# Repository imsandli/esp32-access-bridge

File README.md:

# AccessBridge

**Zigbee dry-contact bridge between a UniFi Access UA-Hub and Home Assistant.**
When the UA-Hub grants access, it closes a potential-free relay contact.
AccessBridge detects the closure and reports it over Zigbee to Zigbee2MQTT.
Home Assistant can then unlatch a Nuki Smart Lock Pro 4. No cloud and no Wi-Fi.

| Part | Name | Version | Licence |
|---|---|---|---|
| Hardware | AccessBridge C6 (Seeed XIAO ESP32C6 carrier) | HW-1.1, PCB Rev B | [CERN-OHL-S-2.0](LICENSE-HARDWARE) |
| Enclosure | 3D-printable case, DIN-rail or wall-screw variant | for HW-1.1 | [CERN-OHL-S-2.0](LICENSE-HARDWARE) |
| Firmware | AccessBridge Zigbee (ESPHome 2026.9.1) | FW-1.0.0 | [MIT](LICENSE) |
| Integrations | Home Assistant blueprints, Zigbee2MQTT notes | - | [MIT](LICENSE) |

> [!WARNING]
> **Not hardware-tested.** Rev B has passed ERC/DRC, the firmware compiles,
> and the Home Assistant logic is covered by automated tests. No board has
> been manufactured or measured yet, and nothing has been tested with a real
> UA-Hub or Nuki. See [compatibility status](#compatibility-status).
>
> **Security:** this device is part of a door access chain. Whoever can short
> the relay wires, or controls your Zigbee/MQTT/Home Assistant, can open the
> door. Read [docs/security.md](docs/security.md) before use. **Never connect
> mains voltage to this board.**

## How it works

```mermaid
flowchart LR
  R[UniFi reader] --> H[UA-Hub]
  H -- "dry relay COM/NO" --> B[AccessBridge C6]
  H -- "12 V LINE (power)" --> B
  B -- "Zigbee end device" --> Z[Zigbee2MQTT >= 2.8.0]
  Z -- MQTT --> HA[Home Assistant<br/>nuki-unlock blueprint]
  HA -- lock.open --> N[Nuki Smart Lock Pro 4]
```

* The contact loop is powered by the board itself (optocoupler, about 3.3 mA),
  so no external voltage is needed on the relay contact.
* The firmware reports the contact **state** and a **pulse counter** of new
  closures. Home Assistant only unlatches on a +1 step of the counter that
  passes the freshness, cooldown and enable checks. Restarts, rejoins and
  restored states never unlatch. Details: [docs/security.md](docs/security.md).
* Power from the UA-Hub 12 V **or** a USB-C charger (J6, power only; the whole
  board including the contact inputs runs on USB for bench tests). Firmware is
  flashed through the XIAO's own USB-C, next to J6 on the same edge.
* Optional: doorbell input (230 V bells via a certified coupling relay; the
  doorbell blueprint also accepts other sensors, see
  [wiring](hardware/docs/wiring.md#doorbell-optional)), selectable contact
  wetting current (JP3-JP5), a
  door-position (DPS) port that works as an input or as an isolated contact
  output, a 12 V open-drain output, and a Qwiic I2C port.

More detail: [docs/architecture.md](docs/architecture.md).

## Supported hardware

| Component | Status |
|---|---|
| UniFi Access **UA-Hub** (classic), LINE 12 V output + dry Lock/Aux relay | designed for; LINE "always on" must be measured on site |
| UA-Hub Door / Gate Hub / Enterprise Hub | not covered (different I/O) |
| Seeed Studio XIAO ESP32C6 | required (socketed) |
| Zigbee2MQTT >= 2.8.0 | designed for (generated definition, no converter) |
| ZHA | not covered by the docs; the firmware uses standard clusters |
| Nuki Smart Lock Pro 4 via the HA Nuki integration (`lock.open`) | designed for |

## Compatibility status

| Level | HW-1.1 Rev B + FW-1.0.0 |
|---|---|
| Statically checked (ERC, DRC with parity, ESPHome config, HA check_config) | **yes** |
| Enclosure fit-checked against the PCB STEP (CI) | **yes** |
| Firmware compiled (CI) | **yes** |
| Software-tested (HA blueprint behaviour tests, 15/15) | **yes** |
| Electrically tested | no |
| Tested with Zigbee2MQTT | no |
| Tested with a real UA-Hub | no |
| Tested with a Nuki | no |

Test plan and record: [docs/testing.md](docs/testing.md).

## Project status (development workflow)

| # | Step | Status |
|---|---|---|
| 1 | Feasibility and datasheet review | done; open points: UA-Hub LINE always-on, XIAO antenna position, Hammond boss positions, live LCSC stock |
| 2 | Schematic | done (`hardware/kicad/accessbridge.kicad_sch`) |
| 3 | ERC | done: 0 errors, 0 warnings |
| 4 | PCB layout | done: 96 x 56 mm, 2 layers (Rev B = Rev A + USB-C power input) |
| 5 | DRC | done: 0 violations, 0 unconnected, 0 parity issues |
| 6 | Fabrication data and BOM | done: Gerber ZIP, drill, JLCPCB BOM/CPL (reproducible, checked in CI) |
| 7 | Firmware implemented and compiled | done (ESPHome 2026.9.1, CI) |
| 8 | Zigbee2MQTT compatibility test | open: needs hardware |
| 9 | Home Assistant example | done (blueprints, check_config, 15 behaviour tests) |
| 10 | Security tests | documented; software part done; hardware part open |
| 11 | Enclosure and mounting check | 3D-printable case (DIN-rail and wall variants) designed and fit-checked against the PCB STEP in CI; not printed yet. Hammond 1591XXD documented as alternative |
| 12 | Release artifacts | workflow ready; first release after the hardware tests |

## Wiring (classic UA-Hub)

| AccessBridge | UA-Hub |
|---|---|
| J1-1 `+12V` | LINE 12V (+) |
| J1-2 `GND` | LINE 12V (-) |
| J1-3 `RELAY COM` | Lock (or Aux) relay COM, **dry mode** |
| J1-4 `RELAY NO` | Lock (or Aux) relay NO |
| J6 USB-C (optional) | any USB-C charger, 5 V, power only, e.g. for bench tests |

Full instructions, doorbell and DPS options: [hardware/docs/wiring.md](hardware/docs/wiring.md).

## Firmware installation

```sh
pip install esphome==2026.9.1
cd firmware/esphome
esphome run accessbridge.yaml      # build + flash over USB-C
```

Or flash a release binary with `esptool.py`. See [docs/installation.md](docs/installation.md).

## Zigbee2MQTT pairing

1. Permit join in Zigbee2MQTT (>= 2.8.0).
2. Power the AccessBridge. The status LED blinks fast until it has joined.
3. The device appears as `esphome` / `accessbridge` with a generated
   definition, with no converter needed.
4. Permit join off. To re-pair, hold PAIR for 5-15 s.

Details and expected exposes: [integrations/zigbee2mqtt](integrations/zigbee2mqtt/README.md).

## Home Assistant example

Import the blueprint [`nuki-unlock.yaml`](integrations/home-assistant/automations/nuki-unlock.yaml)
and select the `relay_pulses` sensor, the `relay_contact` binary sensor and
your Nuki lock. Every ignored pulse is logged with its reason, and unconfirmed
unlatch commands are logged as errors.
See [integrations/home-assistant](integrations/home-assistant/README.md).

## Manufacturing

| | |
|---|---|
| Gerber + drill ZIP (JLCPCB) | [hardware/manufacturing/accessbridge-c6-HW-1.1-revB-gerbers.zip](hardware/manufacturing/accessbridge-c6-HW-1.1-revB-gerbers.zip) |
| JLCPCB BOM / CPL | [bom](hardware/manufacturing/bom/), [pick-and-place](hardware/manufacturing/pick-and-place/) |
| Schematic PDF | [hardware/docs/schematic.pdf](hardware/docs/schematic.pdf) |
| Dimension drawing | [hardware/enclosure/drawings](hardware/enclosure/drawings/accessbridge-c6-dimensions.pdf) |
| Ordering and assembly | [hardware/docs/assembly.md](hardware/docs/assembly.md) |
| Enclosure (3D print, STL/STEP) | [hardware/enclosure](hardware/enclosure/README.md): DIN-rail or wall-screw base, lid, plunger, cable clamp |
| Cost estimate (2/5/10 units) | [hardware/docs/cost-estimate.md](hardware/docs/cost-estimate.md) |
| Releases | [GitHub releases](https://github.com/imsandli/esp32-access-bridge/releases), [releases/README.md](releases/README.md) |

## Repository layout

```
hardware/      KiCad sources, fabrication data (generated), docs, 3D-printed enclosure (CadQuery)
firmware/      ESPHome configuration (FW-1.0.0); ESP-IDF fallback plan
integrations/  Home Assistant blueprints + tests, Zigbee2MQTT notes
docs/          architecture, security, installation, configuration, testing
scripts/       ERC/DRC validation, Gerber/BOM export (KiCad CLI, Docker fallback)
releases/      release process and version scheme
```

## Contributing and licences

See [CONTRIBUTING.md](CONTRIBUTING.md) and [CHANGELOG.md](CHANGELOG.md).
Software (firmware, scripts, integrations, docs) is MIT. Hardware design files
under `hardware/` are CERN-OHL-S-2.0.

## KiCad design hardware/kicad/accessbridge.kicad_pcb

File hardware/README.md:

# AccessBridge C6: hardware

**HW-1.1, PCB Rev B**, KiCad 9.0.9, 2 layers, 96 x 56 mm, CERN-OHL-S-2.0.

Rev B = Rev A plus a **USB-C power input** (J6, 5 V, power only) in a 10 mm
wider right-hand strip. All Rev A parts kept their positions, and Rev A
tracks were kept except around the rewired loop resistors (R10/R14/R18 now on
`V_LOOP`) and R18's neighbourhood.

| | |
|---|---|
| Schematic (PDF) | [docs/schematic.pdf](docs/schematic.pdf) |
| Pinout | [docs/pinout.md](docs/pinout.md) |
| Wiring (UA-Hub) | [docs/wiring.md](docs/wiring.md) |
| Power budget | [docs/power-budget.md](docs/power-budget.md) |
| Assembly / ordering | [docs/assembly.md](docs/assembly.md) |
| Fabrication data | [manufacturing/](manufacturing/README.md) |
| Enclosure (3D print, DIN or wall variant) | [enclosure/](enclosure/README.md) |
| Dimension drawing | [enclosure/drawings/accessbridge-c6-dimensions.pdf](enclosure/drawings/accessbridge-c6-dimensions.pdf) |

## Status

| Check | Status |
|---|---|
| ERC (KiCad 9.0.9, all severities) | **0 errors, 0 warnings** (local and CI) |
| DRC incl. schematic parity (all severities) | **0 violations, 0 unconnected, 0 parity issues** (local and CI) |
| Fabrication data reproducible from sources | **yes**, checked in CI (`scripts/tools/check_generated.py`) |
| Prototype manufactured | no |
| Electrically tested | **no** |

## Source files (`kicad/`)

| File | Content |
|---|---|
| `accessbridge.kicad_pro` | Project: design rules (JLCPCB-safe: 0.2 mm clearance/track, 0.3 mm drill), net classes (Power 0.5 mm, Field 0.3 mm clearance), text variables `HW_VERSION`, `PCB_REV` |
| `accessbridge.kicad_sch` | Schematic (single A3 sheet, framed blocks: connectors, power, MCU, contact inputs, DPS port, output) |
| `accessbridge.kicad_pcb` | Layout |
| `symbols/AccessBridge.kicad_sym` | `XIAO_ESP32C6` symbol (pin names = XIAO D-pin / GPIO) |
| `footprints/AccessBridge.pretty/` | `XIAO_ESP32C6_Socketed` (pad geometry from the Seeed OPL library, 3D = 2x KiCad PinSocket_1x07; includes the antenna keep-out between the pin rows) |
| `sym-lib-table`, `fp-lib-table` | Project libraries via `${KIPRJMOD}` (relative paths) |

All other symbols, footprints and 3D models come from the KiCad 9 standard
libraries (`kicad/kicad:9.0.9-full` contains the 3D models). `3dmodels/` is
reserved for project models; none are needed. The XIAO module itself
has no 3D model: only its sockets are shown.

## Design notes

* **Antenna:** the XIAO's ceramic antenna end (opposite USB-C) has no copper
  between the pin rows, no copper pour below the module end, and a 9 mm
  copper keep-out beyond the module edge on both layers. The module sits about
  8.5 mm above the carrier on its sockets. The exact antenna position on the
  module should be confirmed with a physical sample (open point).
* **Contact inputs:** see [docs/architecture.md](../docs/architecture.md),
  decision A4, and the isolation assessment.
* **Reference designators** are on the Fab layer (assembly drawing
  `docs/assembly-top.pdf`). The silkscreen carries only functional labels,
  so nothing is printed on pads.
* **USB-C power (J6):** VBUS -> PTC F2 (500 mA) + TVS D14 -> D13 into `+5V_XIAO`
  (diode-OR with D3 from the buck) and D16 into `V_LOOP` (diode-OR with D15 from
  +12 V), so the contact inputs also work on USB. CC1/CC2 have 5.1 kΩ to GND
  (USB-C sink). J4 OUT+ stays 12 V only. There is no USB data: the XIAO does not
  route D+/D- to its pins, so firmware goes through the XIAO's own USB-C, which
  sits 15 mm from J6 on the same board edge.
* **Revision marking:** `AccessBridge C6 HW-1.1 Rev B` on the top silkscreen
  and in the title blocks.

## Checks (KiCad CLI)

```sh
scripts/validate-hardware.sh   # ERC + DRC with --schematic-parity, fails on any violation
scripts/export-bom.sh          # full BOM, JLCPCB BOM/CPL, manual assembly list
scripts/export-gerbers.sh      # Gerbers, drill, ZIP, schematic PDF, drawings, 3D renders, PCB STEP
scripts/export-enclosure.sh    # 3D-printed enclosure: STEP/STL, previews, fit check (CadQuery)
```

The scripts use a native KiCad 9 if available, otherwise the pinned Docker
image `kicad/kicad:9.0.9`. The raw commands they wrap are, for example:

```sh
kicad-cli sch erc --severity-all --exit-code-violations hardware/kicad/accessbridge.kicad_sch
kicad-cli pcb drc --severity-all --schematic-parity --exit-code-violations hardware/kicad/accessbridge.kicad_pcb
```

## How Rev A and Rev B were created

Rev A's schematic and initial layout were generated from
[`tools/design.py`](tools/design.py) by the scripts in [`tools/`](tools/README.md)
and routed with Freerouting. Rev B was an incremental change of that board
(`gen_pcb.py update`, then only the new connections routed). From now on, edit
the KiCad files directly.
The generators are kept for transparency only.

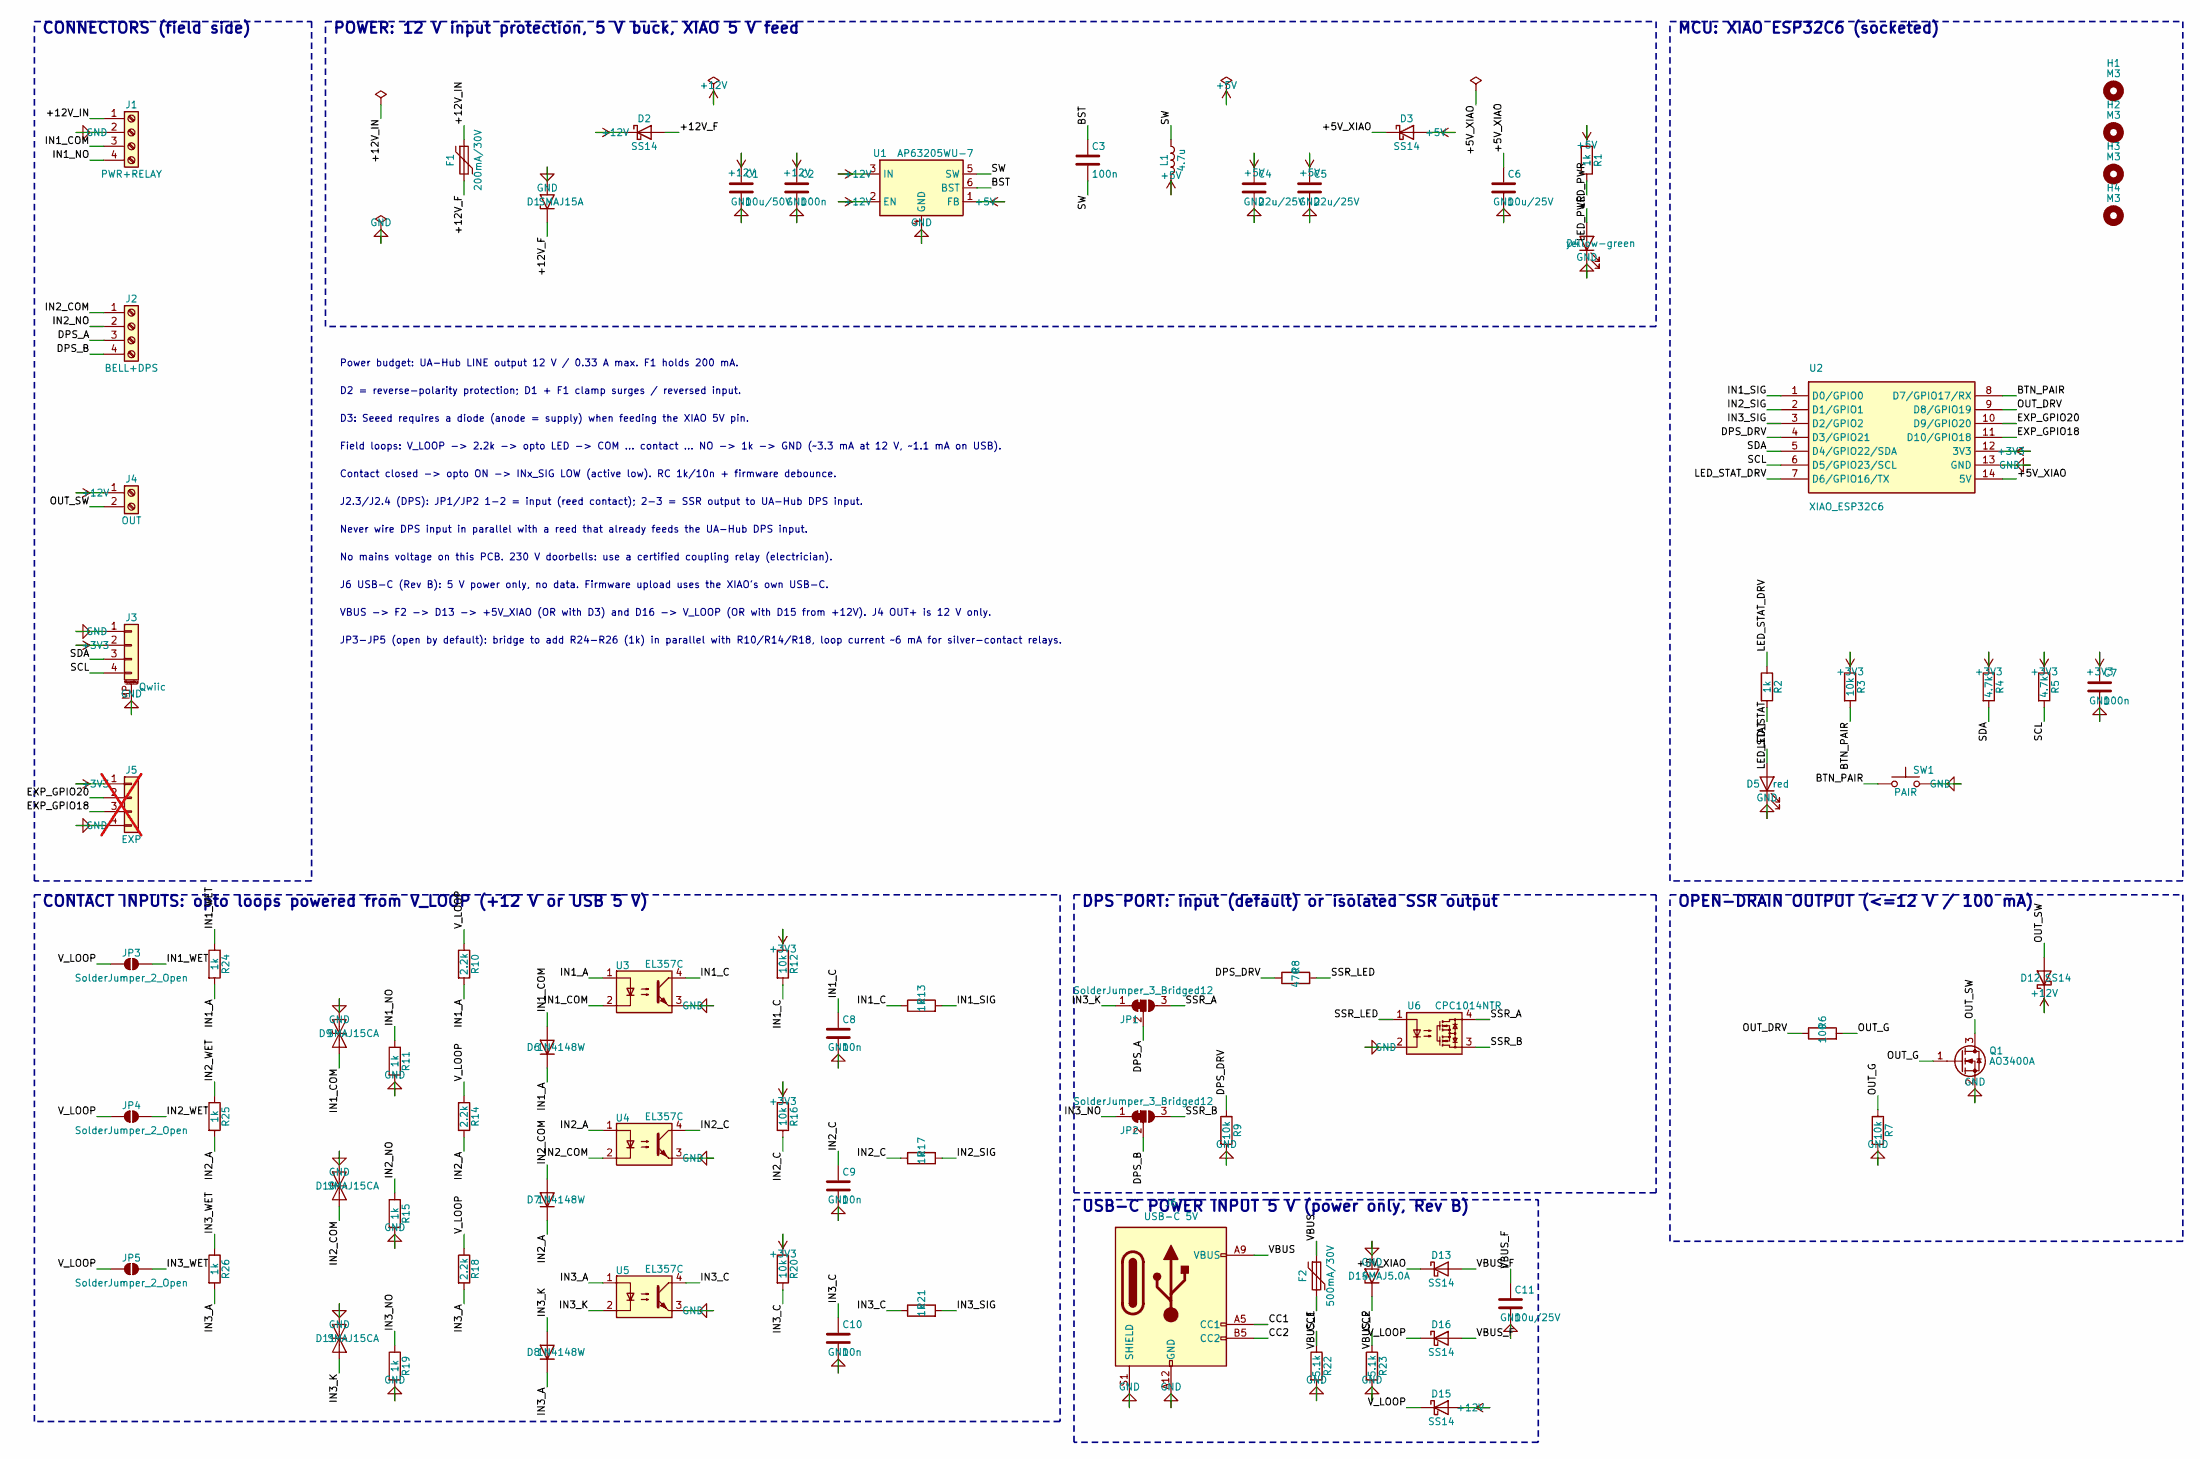
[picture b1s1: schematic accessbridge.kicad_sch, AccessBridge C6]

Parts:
C1: 10u/50V; C_1206_3216Metric; MPN CL31A106KBHNNNE; LCSC C13585
C2, C3, C7: 100n; C_0603_1608Metric; MPN CC0603KRX7R9BB104; LCSC C14663
C4, C5: 22u/25V; C_0805_2012Metric; MPN CL21A226MAQNNNE; LCSC C45783
C6, C11: 10u/25V; C_0805_2012Metric; MPN CL21A106KAYNNNE; LCSC C15850
C8, C9, C10: 10n; C_0603_1608Metric; MPN 0603B103K500NT; LCSC C57112
D1: SMAJ15A; D_SMA; MPN SMAJ15A; LCSC C148216
D2, D3, D12, D13, D15, D16: SS14; D_SMA; MPN SS14; LCSC C2480
D4: yellow-green; LED_0603_1608Metric; MPN KT-0603YG; LCSC C2289
D5: red; LED_0603_1608Metric; MPN KT-0603R; LCSC C2286
D6, D7, D8: 1N4148W; D_SOD-123; MPN 1N4148W; LCSC C81598
D9, D10, D11: SMAJ15CA; D_SMA; MPN SMAJ15CA; LCSC C110044
D14: SMAJ5.0A; D_SMA; MPN SMAJ5.0A; LCSC C83329
F1: 200mA/30V; Fuse_1206_3216Metric; MPN BSMD1206-020-30V; LCSC C883118
F2: 500mA/30V; Fuse_1206_3216Metric; MPN BSMD1206-050-30V; LCSC C883126
H1, H2, H3, H4: M3; MountingHole_3.2mm_M3; MPN M3 mounting hole; LCSC_Status pcb
J1: PWR+RELAY; TerminalBlock_Phoenix_MKDS-1,5-4-5.08_1x04_P5.08mm_Horizont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; MPN MKDS 1,5/ 4-5,08 (1715747) or 5.08 mm e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; LCSC_Status manual
J2: BELL+DPS; TerminalBlock_Phoenix_MKDS-1,5-4-5.08_1x04_P5.08mm_Horizont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; MPN MKDS 1,5/ 4-5,08 (1715747) or 5.08 mm e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; LCSC_Status manual
J3: Qwiic; JST_SH_SM04B-SRSS-TB_1x04-1MP_P1.00mm_Horizontal; MPN SM04B-SRSS-TB(LF)(SN); LCSC C160404
J4: OUT; TerminalBlock_Phoenix_MKDS-1,5-2-5.08_1x02_P5.08mm_Horizont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; MPN MKDS 1,5/ 2-5,08 (1715721) or 5.08 mm e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; LCSC_Status manual
J5: EXP; PinHeader_1x04_P2.54mm_Vertical; MPN 2.54 mm 1x4 pin header; LCSC_Status manual; not fitted
J6: USB-C 5V; USB_C_Receptacle_GCT_USB4125-xx-x_6P_TopMnt_Horizontal; MPN USB4125-GF-A; LCSC C3151650
JP1, JP2: SolderJumper_3_Bridged12; SolderJumper-3_P1.3mm_Bridged12_RoundedPad1.0x1.5mm_NumberL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; MPN PCB solder jumper; LCSC_Status pcb
JP3, JP4, JP5: SolderJumper_2_Open; SolderJumper-2_P1.3mm_Open_RoundedPad1.0x1.5mm; MPN PCB solder jumper; LCSC_Status pcb
L1: 4.7u; L_Changjiang_FNR4030S; MPN SWPA4030S4R7MT; LCSC C57269
Q1: AO3400A; SOT-23; MPN AO3400A; LCSC C20917
R1, R2, R11, R13, R15, R17, R19, R21: 1k; R_0603_1608Metric; MPN 0603WAF1001T5E; LCSC C21190
R3, R7, R9, R12, R16, R20: 10k; R_0603_1608Metric; MPN 0603WAF1002T5E; LCSC C25804
R4, R5: 4.7k; R_0603_1608Metric; MPN 0603WAF4701T5E; LCSC C23162
R6: 100; R_0603_1608Metric; MPN 0603WAF1000T5E; LCSC C22775
R8: 470; R_0603_1608Metric; MPN 0603WAF4700T5E; LCSC C23179
R10, R14, R18: 2.2k; R_0603_1608Metric; MPN 0603WAF2201T5E; LCSC C4190
R22, R23: 5.1k; R_0603_1608Metric; MPN 0603WAF5101T5E; LCSC C23186
R24, R25, R26: 1k; R_1206_3216Metric; MPN 1206W4F1001T5E; LCSC C4410
SW1: PAIR; SW_Push_1P1T_XKB_TS-1187A; MPN TS-1187A-B-A-B; LCSC C318884
U1: AP63205WU-7; TSOT-23-6; MPN AP63205WU-7; LCSC C2071056
U2: XIAO_ESP32C6; XIAO_ESP32C6_Socketed; MPN 113991254 (module) + 2x female header 1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; LCSC_Status manual
U3, U4, U5: EL357C; SO-4_4.4x3.6mm_P2.54mm; MPN EL357C; LCSC C725794
U6: CPC1014NTR; SOP-4_3.8x4.1mm_P2.54mm; MPN CPC1014NTR; LCSC C2760365

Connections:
+3V3: C7.1, J3.2, J5.1, R3.1, R4.1, R5.1, R12.1, R16.1, R20.1, U2.12 (3V3)
+5V: C4.1, C5.1, D3.2 (A), L1.2, R1.1, U1.1 (FB)
+12V: C1.1, C2.1, D2.1 (K), D12.1 (K), D15.2 (A), J4.1, U1.2 (EN), U1.3 (IN)
/+5V_XIAO: C6.1, D3.1 (K), D13.1 (K), U2.14 (5V)
/+12V_F: D1.1 (A1), D2.2 (A), F1.2
/+12V_IN: F1.1, J1.1
/BST: C3.1, U1.6 (BST)
/BTN_PAIR: R3.2, SW1.1, U2.8 (D7/GPIO17/RX)
/CC1: J6.A5 (CC1), R22.1
/CC2: J6.B5 (CC2), R23.1
/DPS_A: J2.3, JP1.2 (C)
/DPS_B: J2.4, JP2.2 (C)
/DPS_DRV: R8.1, R9.1, U2.4 (D3/GPIO21)
/EXP_GPIO18: J5.3, U2.11 (D10/GPIO18)
/EXP_GPIO20: J5.2, U2.10 (D9/GPIO20)
/IN1_A: D6.1 (K), R10.2, R24.2, U3.1
/IN1_C: C8.1, R12.2, R13.1, U3.4
/IN1_COM: D6.2 (A), D9.1 (A1), J1.3, U3.2
/IN1_NO: J1.4, R11.1
/IN1_SIG: R13.2, U2.1 (D0/GPIO0)
/IN1_WET: JP3.2 (B), R24.1
/IN2_A: D7.1 (K), R14.2, R25.2, U4.1
/IN2_C: C9.1, R16.2, R17.1, U4.4
/IN2_COM: D7.2 (A), D10.1 (A1), J2.1, U4.2
/IN2_NO: J2.2, R15.1
/IN2_SIG: R17.2, U2.2 (D1/GPIO1)
/IN2_WET: JP4.2 (B), R25.1
/IN3_A: D8.1 (K), R18.2, R26.2, U5.1
/IN3_C: C10.1, R20.2, R21.1, U5.4
/IN3_K: D8.2 (A), D11.1 (A1), JP1.1 (A), U5.2
/IN3_NO: JP2.1 (A), R19.1
/IN3_SIG: R21.2, U2.3 (D2/GPIO2)
/IN3_WET: JP5.2 (B), R26.1
/LED_PWR: D4.2 (A), R1.2
/LED_STAT: D5.2 (A), R2.2
/LED_STAT_DRV: R2.1, U2.7 (D6/GPIO16/TX)
/OUT_DRV: R6.1, U2.9 (D8/GPIO19)
/OUT_G: Q1.1 (G), R6.2, R7.1
/OUT_SW: D12.2 (A), J4.2, Q1.3 (D)
/SCL: J3.4, R5.2, U2.6 (D5/GPIO23/SCL)
/SDA: J3.3, R4.2, U2.5 (D4/GPIO22/SDA)
/SSR_A: JP1.3 (B), U6.4
/SSR_B: JP2.3 (B), U6.3
/SSR_LED: R8.2, U6.1
/SW: C3.2, L1.1, U1.5 (SW)
/VBUS: F2.1, J6.A9 (VBUS), J6.B9 (VBUS)
/VBUS_F: C11.1, D13.2 (A), D14.1 (A1), D16.2 (A), F2.2
/V_LOOP: D15.1 (K), D16.1 (K), JP3.1 (A), JP4.1 (A), JP5.1 (A), R10.1, R14.1, R18.1
GND: C1.2, C2.2, C4.2, C5.2, C6.2, C7.2, C8.2, C9.2, C10.2, C11.2, D1.2 (A2), D4.1 (K), D5.1 (K), D9.2 (A2), D10.2 (A2), D11.2 (A2), D14.2 (A2), J1.2, J3.1, J3.MP (MountPin), J5.4, J6.A12 (GND), J6.B12 (GND), J6.S1 (SHIELD), Q1.2 (S), R7.2, R9.2, R11.2, R15.2, R19.2, R22.2, R23.2, SW1.2, U1.4 (GND), U2.13 (GND), U3.3, U4.3, U5.3, U6.2

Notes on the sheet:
CONNECTORS (field side)
POWER: 12 V input protection, 5 V buck, XIAO 5 V feed
MCU: XIAO ESP32C6 (socketed)
CONTACT INPUTS: opto loops powered from V_LOOP (+12 V or USB 5 V)
DPS PORT: input (default) or isolated SSR output
OPEN-DRAIN OUTPUT (<=12 V / 100 mA)
USB-C POWER INPUT 5 V (power only, Rev B)
Power budget: UA-Hub LINE output 12 V / 0.33 A max. F1 holds 200 mA.
D2 = reverse-polarity protection; D1 + F1 clamp surges / reversed input.
D3: Seeed requires a diode (anode = supply) when feeding the XIAO 5V pin.
Field loops: V_LOOP -> 2.2k -> opto LED -> COM ... contact ... NO -> 1k -> GND (~3.3 mA at 12 V, ~1.1 mA on USB).
Contact closed -> opto ON -> INx_SIG LOW (active low). RC 1k/10n + firmware debounce.
J2.3/J2.4 (DPS): JP1/JP2 1-2 = input (reed contact); 2-3 = SSR output to UA-Hub DPS input.
Never wire DPS input in parallel with a reed that already feeds the UA-Hub DPS input.
No mains voltage on this PCB. 230 V doorbells: use a certified coupling relay (electrician).
J6 USB-C (Rev B): 5 V power only, no data. Firmware upload uses the XIAO's own USB-C.
VBUS -> F2 -> D13 -> +5V_XIAO (OR with D3) and D16 -> V_LOOP (OR with D15 from +12V). J4 OUT+ is 12 V only.
JP3-JP5 (open by default): bridge to add R24-R26 (1k) in parallel with R10/R14/R18, loop current ~6 mA for silver-contact relays.

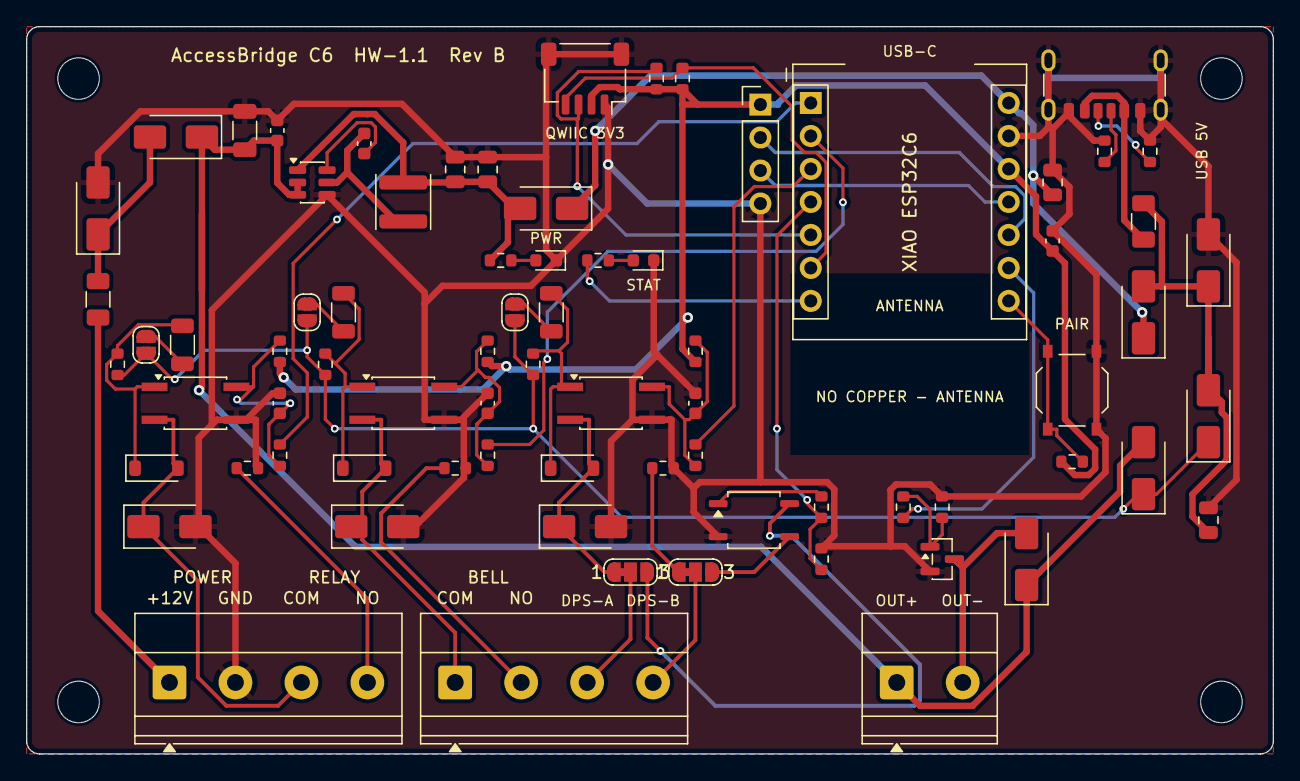
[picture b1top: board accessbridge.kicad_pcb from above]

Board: 2 copper layers, 96.0 x 56.0 mm, 79 parts (0 on the bottom side), 49 nets.

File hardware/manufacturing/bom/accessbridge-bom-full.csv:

"Designator","Value","Footprint","Manufacturer","MPN","LCSC","LCSC status","Qty","DNP"
"C1","10u/50V","Capacitor_SMD:C_1206_3216Metric","Samsung","CL31A106KBHNNNE","C13585","secondary","1",""
"C2,C3,C7","100n","Capacitor_SMD:C_0603_1608Metric","YAGEO","CC0603KRX7R9BB104","C14663","confirmed","3",""
"C4,C5","22u/25V","Capacitor_SMD:C_0805_2012Metric","Samsung","CL21A226MAQNNNE","C45783","secondary","2",""
"C6,C11","10u/25V","Capacitor_SMD:C_0805_2012Metric","Samsung","CL21A106KAYNNNE","C15850","secondary","2",""
"C8,C9,C10","10n","Capacitor_SMD:C_0603_1608Metric","FH","0603B103K500NT","C57112","confirmed","3",""
"D1","SMAJ15A","Diode_SMD:D_SMA","Littelfuse","SMAJ15A","C148216","confirmed","1",""
"D2,D3,D12,D13,D15,D16","SS14","Diode_SMD:D_SMA","MDD","SS14","C2480","confirmed","6",""
"D4","yellow-green","LED_SMD:LED_0603_1608Metric","Hubei KENTO","KT-0603YG","C2289","confirmed","1",""
"D5","red","LED_SMD:LED_0603_1608Metric","Hubei KENTO","KT-0603R","C2286","secondary","1",""
"D6,D7,D8","1N4148W","Diode_SMD:D_SOD-123","ST(Semtech)","1N4148W","C81598","confirmed","3",""
"D9,D10,D11","SMAJ15CA","Diode_SMD:D_SMA","MDD","SMAJ15CA","C110044","confirmed","3",""
"D14","SMAJ5.0A","Diode_SMD:D_SMA","Littelfuse","SMAJ5.0A","C83329","confirmed","1",""
"F1","200mA/30V","Fuse:Fuse_1206_3216Metric","BHFUSE","BSMD1206-020-30V","C883118","confirmed","1",""
"F2","500mA/30V","Fuse:Fuse_1206_3216Metric","BHFUSE","BSMD1206-050-30V","C883126","confirmed","1",""
"J1","PWR+RELAY","TerminalBlock_Phoenix:TerminalBlock_Phoenix_MKDS-1,5-4-5.08_1x04_P5.08mm_Horizontal","Phoenix Contact","MKDS 1,5/ 4-5,08 (1715747) or 5.08 mm equivalent","","manual","1",""
"J2","BELL+DPS","TerminalBlock_Phoenix:TerminalBlock_Phoenix_MKDS-1,5-4-5.08_1x04_P5.08mm_Horizontal","Phoenix Contact","MKDS 1,5/ 4-5,08 (1715747) or 5.08 mm equivalent","","manual","1",""
"J3","Qwiic","Connector_JST:JST_SH_SM04B-SRSS-TB_1x04-1MP_P1.00mm_Horizontal","JST","SM04B-SRSS-TB(LF)(SN)","C160404","confirmed","1",""
"J4","OUT","TerminalBlock_Phoenix:TerminalBlock_Phoenix_MKDS-1,5-2-5.08_1x02_P5.08mm_Horizontal","Phoenix Contact","MKDS 1,5/ 2-5,08 (1715721) or 5.08 mm equivalent","","manual","1",""
"J5","EXP","Connector_PinHeader_2.54mm:PinHeader_1x04_P2.54mm_Vertical","generic","2.54 mm 1x4 pin header","","manual","1","DNP"
"J6","USB-C 5V","Connector_USB:USB_C_Receptacle_GCT_USB4125-xx-x_6P_TopMnt_Horizontal","GCT","USB4125-GF-A","C3151650","confirmed","1",""
"L1","4.7u","Inductor_SMD:L_Changjiang_FNR4030S","Sunlord","SWPA4030S4R7MT","C57269","confirmed","1",""
"Q1","AO3400A","Package_TO_SOT_SMD:SOT-23","AOS","AO3400A","C20917","confirmed","1",""
"R1,R2,R11,R13,R15,R17,R19,R21","1k","Resistor_SMD:R_0603_1608Metric","UNI-ROYAL","0603WAF1001T5E","C21190","confirmed","8",""
"R3,R7,R9,R12,R16,R20","10k","Resistor_SMD:R_0603_1608Metric","UNI-ROYAL","0603WAF1002T5E","C25804","confirmed","6",""
"R4,R5","4.7k","Resistor_SMD:R_0603_1608Metric","UNI-ROYAL","0603WAF4701T5E","C23162","confirmed","2",""
"R6","100","Resistor_SMD:R_0603_1608Metric","UNI-ROYAL","0603WAF1000T5E","C22775","secondary","1",""
"R8","470","Resistor_SMD:R_0603_1608Metric","UNI-ROYAL","0603WAF4700T5E","C23179","confirmed","1",""
"R10,R14,R18","2.2k","Resistor_SMD:R_0603_1608Metric","UNI-ROYAL","0603WAF2201T5E","C4190","secondary","3",""
"R22,R23","5.1k","Resistor_SMD:R_0603_1608Metric","UNI-ROYAL","0603WAF5101T5E","C23186","confirmed","2",""
"R24,R25,R26","1k","Resistor_SMD:R_1206_3216Metric","UNI-ROYAL","1206W4F1001T5E","C4410","confirmed","3",""
"SW1","PAIR","Button_Switch_SMD:SW_Push_1P1T_XKB_TS-1187A","XKB","TS-1187A-B-A-B","C318884","confirmed","1",""
"U1","AP63205WU-7","Package_TO_SOT_SMD:TSOT-23-6","Diodes Inc.","AP63205WU-7","C2071056","confirmed","1",""
"U2","XIAO_ESP32C6","AccessBridge:XIAO_ESP32C6_Socketed","Seeed Studio","113991254 (module) + 2x female header 1x7 2.54 mm","","manual","1",""
"U3,U4,U5","EL357C","Package_SO:SO-4_4.4x3.6mm_P2.54mm","UMW","EL357C","C725794","confirmed","3",""
"U6","CPC1014NTR","Package_SO:SOP-4_3.8x4.1mm_P2.54mm","Littelfuse/IXYS","CPC1014NTR","C2760365","confirmed","1",""

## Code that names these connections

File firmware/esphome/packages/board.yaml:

# AccessBridge C6 HW-1.1 / Rev B (same GPIO map as HW-1.0 / Rev A): board definition and the ONLY place where
# GPIO numbers are defined. Mapping verified against the Seeed XIAO ESP32C6
# wiki (D-pin -> GPIO) and hardware/kicad/accessbridge.kicad_sch.
#
#   XIAO pin  GPIO    Net            Function
#   D0        GPIO0   IN1_SIG        UA-Hub relay contact (opto U3, active low)
#   D1        GPIO1   IN2_SIG        doorbell contact     (opto U4, active low)
#   D2        GPIO2   IN3_SIG        DPS reed contact     (opto U5, active low)
#   D3        GPIO21  DPS_DRV        DPS SSR U6 LED (high = SSR closed)
#   D4        GPIO22  SDA            Qwiic J3 (4.7k pull-up)
#   D5        GPIO23  SCL            Qwiic J3 (4.7k pull-up)
#   D6        GPIO16  LED_STAT_DRV   red status LED D5 (high = on)
#   D7        GPIO17  BTN_PAIR       PAIR button SW1 (low = pressed, 10k pull-up)
#   D8        GPIO19  OUT_DRV        open-drain output Q1 (high = output on)
#   D9        GPIO20  EXP_GPIO20     J5 expansion header (not populated)
#   D10       GPIO18  EXP_GPIO18     J5 expansion header (not populated)
#   -         GPIO3   (on module)    RF switch enable (low = enabled)
#   -         GPIO14  (on module)    antenna select (low = ceramic, high = U.FL)

substitutions:
  pin_in_relay: GPIO0
  pin_in_bell: GPIO1
  pin_in_dps: GPIO2
  pin_dps_ssr: GPIO21
  pin_sda: GPIO22
  pin_scl: GPIO23
  pin_status_led: GPIO16
  pin_pair_button: GPIO17
  pin_out: GPIO19
  # false = on-board ceramic antenna, true = external U.FL antenna
  use_external_antenna: "false"

esp32:
  board: seeed_xiao_esp32c6
  variant: esp32c6
  framework:
    type: esp-idf

esphome:
  on_boot:
    # Before anything else: drive the XIAO RF switch (Seeed wiki: GPIO3 low
    # enables the switch, GPIO14 selects ceramic (low) or U.FL (high) antenna).
    priority: 1000
    then:
      - lambda: |-
          gpio_reset_pin(GPIO_NUM_3);
          gpio_set_direction(GPIO_NUM_3, GPIO_MODE_OUTPUT);
          gpio_set_level(GPIO_NUM_3, 0);
          gpio_reset_pin(GPIO_NUM_14);
          gpio_set_direction(GPIO_NUM_14, GPIO_MODE_OUTPUT);
          gpio_set_level(GPIO_NUM_14, ${use_external_antenna} ? 1 : 0);
          ESP_LOGI("board", "AccessBridge C6 HW-1.x, antenna: %s", ${use_external_antenna} ? "U.FL" : "ceramic");

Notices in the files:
hardware/kicad/accessbridge.kicad_pcb:
License: CERN-OHL-S-2.0
AccessBridge C6 HW-1.1 Rev B - CERN-OHL-S-2.0
